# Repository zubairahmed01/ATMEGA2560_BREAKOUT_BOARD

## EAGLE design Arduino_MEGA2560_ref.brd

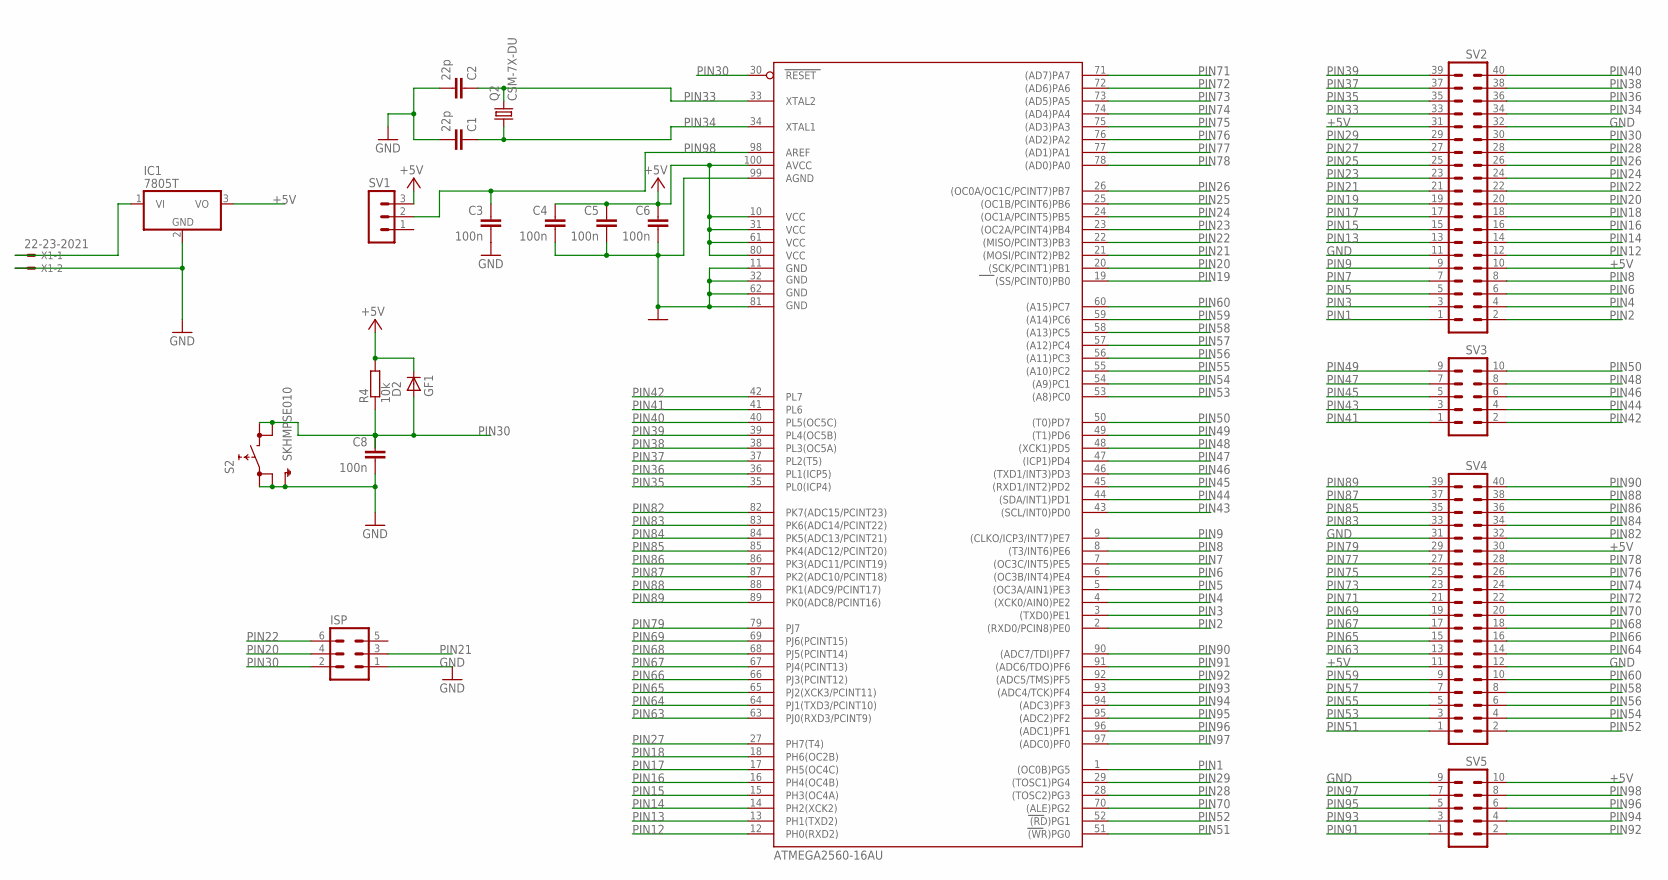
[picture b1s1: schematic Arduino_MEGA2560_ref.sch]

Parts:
C1, C2: 22p; C0603-ROUND
C3, C4, C5, C6, C8: 100n; C0603-ROUND
D2: GF1; SMA-DO214AC
IC1: 7805T; TO220H
IC3: ATMEGA2560-16AU; TQFP100
ISP: MA03-2
Q2: CSM-7X-DU
R4: 10k; SMS-0
S2: SKHMPSE010; SKHMPXE010
SV1: MA03-1
SV2, SV4: MA20-2
SV3, SV5: MA05-2
X1: 22-23-2021

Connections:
+5V: C4.1, C5.1, C6.1, D2.K (C), IC1.3 (VO), IC3.10 (VCC), IC3.31 (VCC1), IC3.61 (VCC2), IC3.80 (VCC3), IC3.100 (AVCC), R4.1, SV1.3, SV2.10, SV2.31, SV4.11, SV4.30, SV5.10
GND: C1.2, C2.2, C3.2, C4.2, C5.2, C6.2, C8.2, IC1.2 (GND), IC3.11 (GND), IC3.32 (GND1), IC3.62 (GND2), IC3.81 (GND3), IC3.99 (AGND), ISP.1, S2.1 (1.1), S2.2 (1.2), S2.5 (SH), SV2.11, SV2.32, SV4.12, SV4.31, SV5.9, X1.2
unnamed: IC1.1 (VI), X1.1
PIN1: IC3.1 ((OC0B)PG5), SV2.1
PIN2: IC3.2 ((RXD0/PCIN8)PE0), SV2.2
PIN3: IC3.3 ((TXD0)PE1), SV2.3
PIN4: IC3.4 ((XCK0/AIN0)PE2), SV2.4
PIN5: IC3.5 ((OC3A/AIN1)PE3), SV2.5
PIN6: IC3.6 ((OC3B/INT4)PE4), SV2.6
PIN7: IC3.7 ((OC3C/INT5)PE5), SV2.7
PIN8: IC3.8 ((T3/INT6)PE6), SV2.8
PIN9: IC3.9 ((CLKO/ICP3/INT7)PE7), SV2.9
PIN12: IC3.12 (PH0(RXD2)), SV2.12
PIN13: IC3.13 (PH1(TXD2)), SV2.13
PIN14: IC3.14 (PH2(XCK2)), SV2.14
PIN15: IC3.15 (PH3(OC4A)), SV2.15
PIN16: IC3.16 (PH4(OC4B)), SV2.16
PIN17: IC3.17 (PH5(OC4C)), SV2.17
PIN18: IC3.18 (PH6(OC2B)), SV2.18
PIN19: IC3.19 ((SS/PCINT0)PB0), SV2.19
PIN20: IC3.20 ((SCK/PCINT1)PB1), ISP.4, SV2.20
PIN21: IC3.21 ((MOSI/PCINT2)PB2), ISP.3, SV2.21
PIN22: IC3.22 ((MISO/PCINT3)PB3), ISP.6, SV2.22
PIN23: IC3.23 ((OC2A/PCINT4)PB4), SV2.23
PIN24: IC3.24 ((OC1A/PCINT5)PB5), SV2.24
PIN25: IC3.25 ((OC1B/PCINT6)PB6), SV2.25
PIN26: IC3.26 ((OC0A/OC1C/PCINT7)PB7), SV2.26
PIN27: IC3.27 (PH7(T4)), SV2.27
PIN28: IC3.28 ((TOSC2)PG3), SV2.28
PIN29: IC3.29 ((TOSC1)PG4), SV2.29
PIN30: C8.1, D2.A, IC3.30 (RESET), ISP.2, R4.2, S2.3 (2.1), S2.4 (2.2), SV2.30
PIN33: C2.1, IC3.33 (XTAL2), Q2.2, SV2.33
PIN34: C1.1, IC3.34 (XTAL1), Q2.1, SV2.34
PIN35: IC3.35 (PL0(ICP4)), SV2.35
PIN36: IC3.36 (PL1(ICP5)), SV2.36
PIN37: IC3.37 (PL2(T5)), SV2.37
PIN38: IC3.38 (PL3(OC5A)), SV2.38
PIN39: IC3.39 (PL4(OC5B)), SV2.39
PIN40: IC3.40 (PL5(OC5C)), SV2.40
PIN41: IC3.41 (PL6), SV3.1
PIN42: IC3.42 (PL7), SV3.2
PIN43: IC3.43 ((SCL/INT0)PD0), SV3.3
PIN44: IC3.44 ((SDA/INT1)PD1), SV3.4
PIN45: IC3.45 ((RXD1/INT2)PD2), SV3.5
PIN46: IC3.46 ((TXD1/INT3)PD3), SV3.6
PIN47: IC3.47 ((ICP1)PD4), SV3.7
PIN48: IC3.48 ((XCK1)PD5), SV3.8
PIN49: IC3.49 ((T1)PD6), SV3.9
PIN50: IC3.50 ((T0)PD7), SV3.10
PIN51: IC3.51 ((WR)PG0), SV4.1
PIN52: IC3.52 ((RD)PG1), SV4.2
PIN53: IC3.53 ((A8)PC0), SV4.3
PIN54: IC3.54 ((A9)PC1), SV4.4
PIN55: IC3.55 ((A10)PC2), SV4.5
PIN56: IC3.56 ((A11)PC3), SV4.6
PIN57: IC3.57 ((A12)PC4), SV4.7
PIN58: IC3.58 ((A13)PC5), SV4.8
PIN59: IC3.59 ((A14)PC6), SV4.9
PIN60: IC3.60 ((A15)PC7), SV4.10
PIN63: IC3.63 (PJ0(RXD3/PCINT9)), SV4.13
PIN64: IC3.64 (PJ1(TXD3/PCINT10)), SV4.14
PIN65: IC3.65 (PJ2(XCK3/PCINT11)), SV4.15
PIN66: IC3.66 (PJ3(PCINT12)), SV4.16
PIN67: IC3.67 (PJ4(PCINT13)), SV4.17
PIN68: IC3.68 (PJ5(PCINT14)), SV4.18
PIN69: IC3.69 (PJ6(PCINT15)), SV4.19
PIN70: IC3.70 ((ALE)PG2), SV4.20
PIN71: IC3.71 ((AD7)PA7), SV4.21
PIN72: IC3.72 ((AD6)PA6), SV4.22
PIN73: IC3.73 ((AD5)PA5), SV4.23
PIN74: IC3.74 ((AD4)PA4), SV4.24
PIN75: IC3.75 ((AD3)PA3), SV4.25
PIN76: IC3.76 ((AD2)PA2), SV4.26
PIN77: IC3.77 ((AD1)PA1), SV4.27
PIN78: IC3.78 ((AD0)PA0), SV4.28
PIN79: IC3.79 (PJ7), SV4.29
PIN82: IC3.82 (PK7(ADC15/PCINT23)), SV4.32
PIN83: IC3.83 (PK6(ADC14/PCINT22)), SV4.33
PIN84: IC3.84 (PK5(ADC13/PCINT21)), SV4.34
PIN85: IC3.85 (PK4(ADC12/PCINT20)), SV4.35
PIN86: IC3.86 (PK3(ADC11/PCINT19)), SV4.36
PIN87: IC3.87 (PK2(ADC10/PCINT18)), SV4.37
PIN88: IC3.88 (PK1(ADC9/PCINT17)), SV4.38
PIN89: IC3.89 (PK0(ADC8/PCINT16)), SV4.39
PIN90: IC3.90 ((ADC7/TDI)PF7), SV4.40
PIN91: IC3.91 ((ADC6/TDO)PF6), SV5.1
PIN92: IC3.92 ((ADC5/TMS)PF5), SV5.2
PIN93: IC3.93 ((ADC4/TCK)PF4), SV5.3
PIN94: IC3.94 ((ADC3)PF3), SV5.4
PIN95: IC3.95 ((ADC2)PF2), SV5.5
PIN96: IC3.96 ((ADC1)PF1), SV5.6
PIN97: IC3.97 ((ADC0)PF0), SV5.7
PIN98: C3.1, IC3.98 (AREF), SV1.2, SV5.8

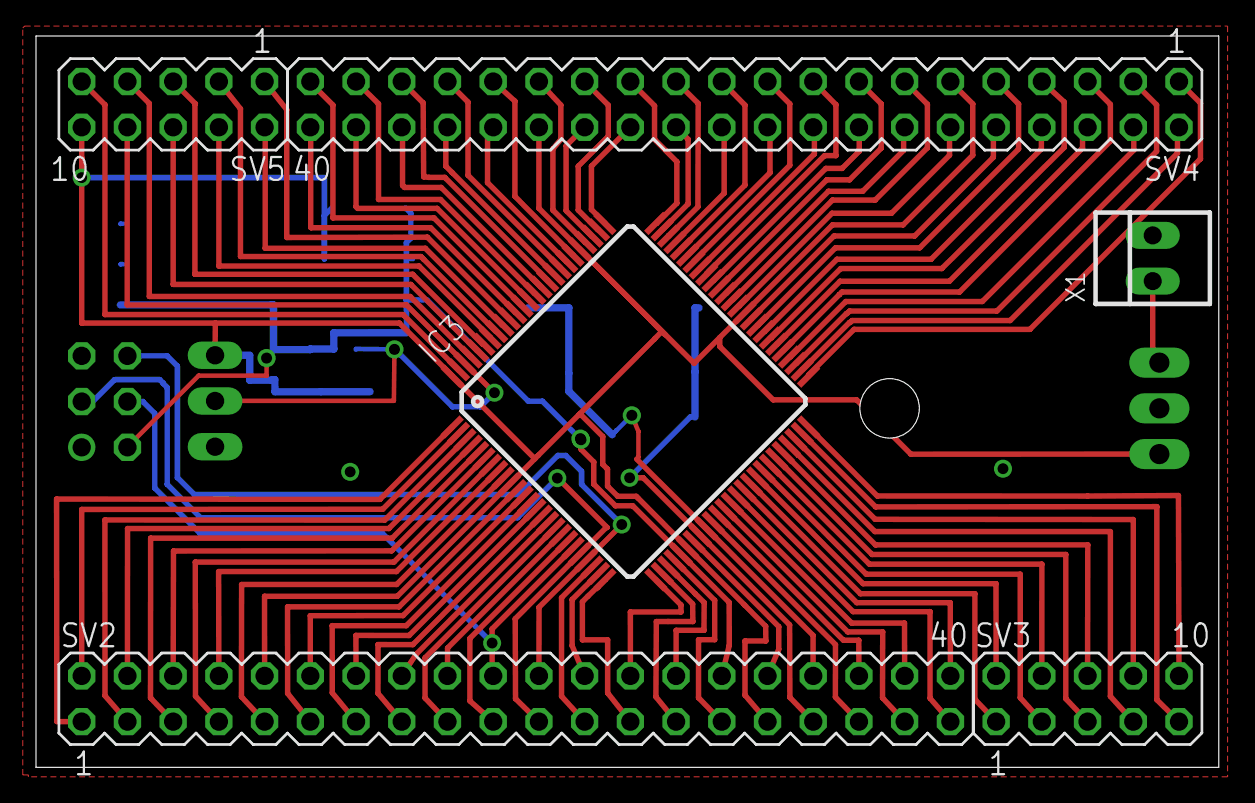
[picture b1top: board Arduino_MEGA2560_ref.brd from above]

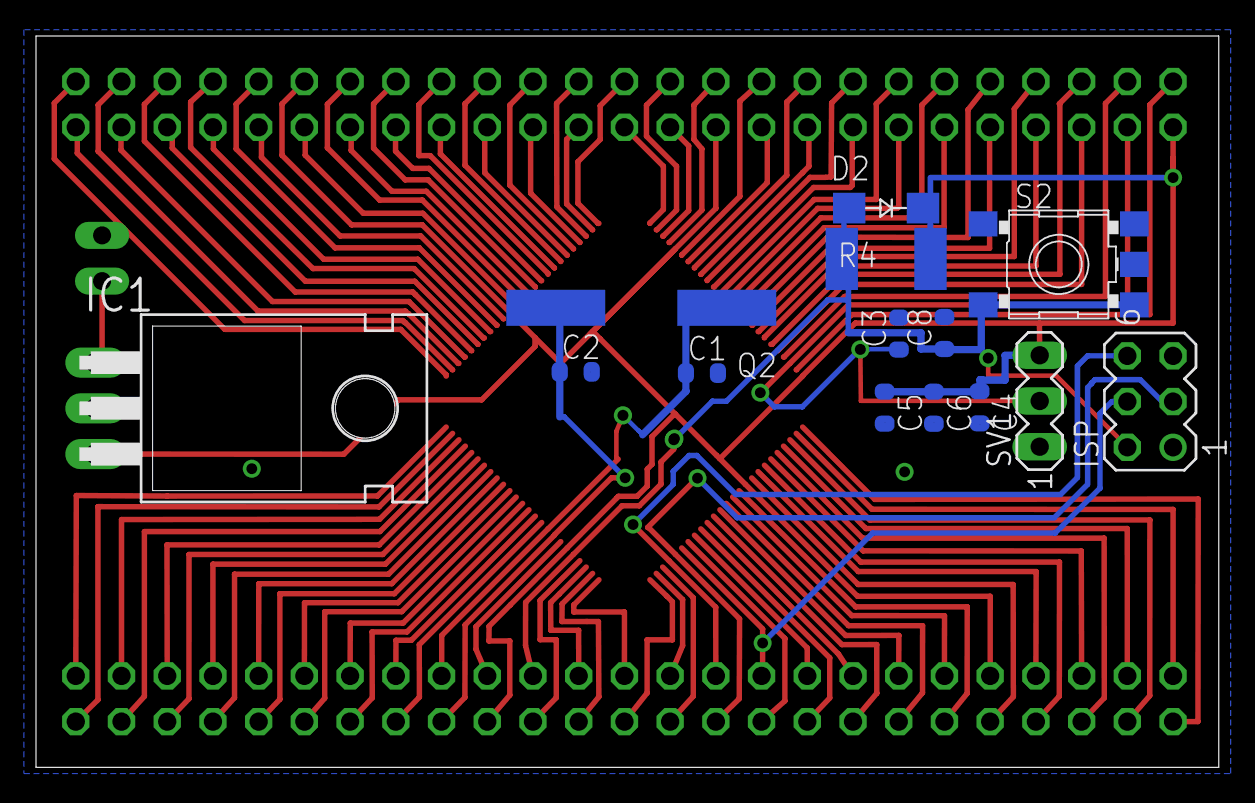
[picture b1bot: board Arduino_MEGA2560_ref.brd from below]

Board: 2 copper layers, 65.7 x 40.6 mm, 20 parts (14 on the bottom side), 93 nets.

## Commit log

2014-02-02 Atmega2560
    it is a board for Atmega2560.
